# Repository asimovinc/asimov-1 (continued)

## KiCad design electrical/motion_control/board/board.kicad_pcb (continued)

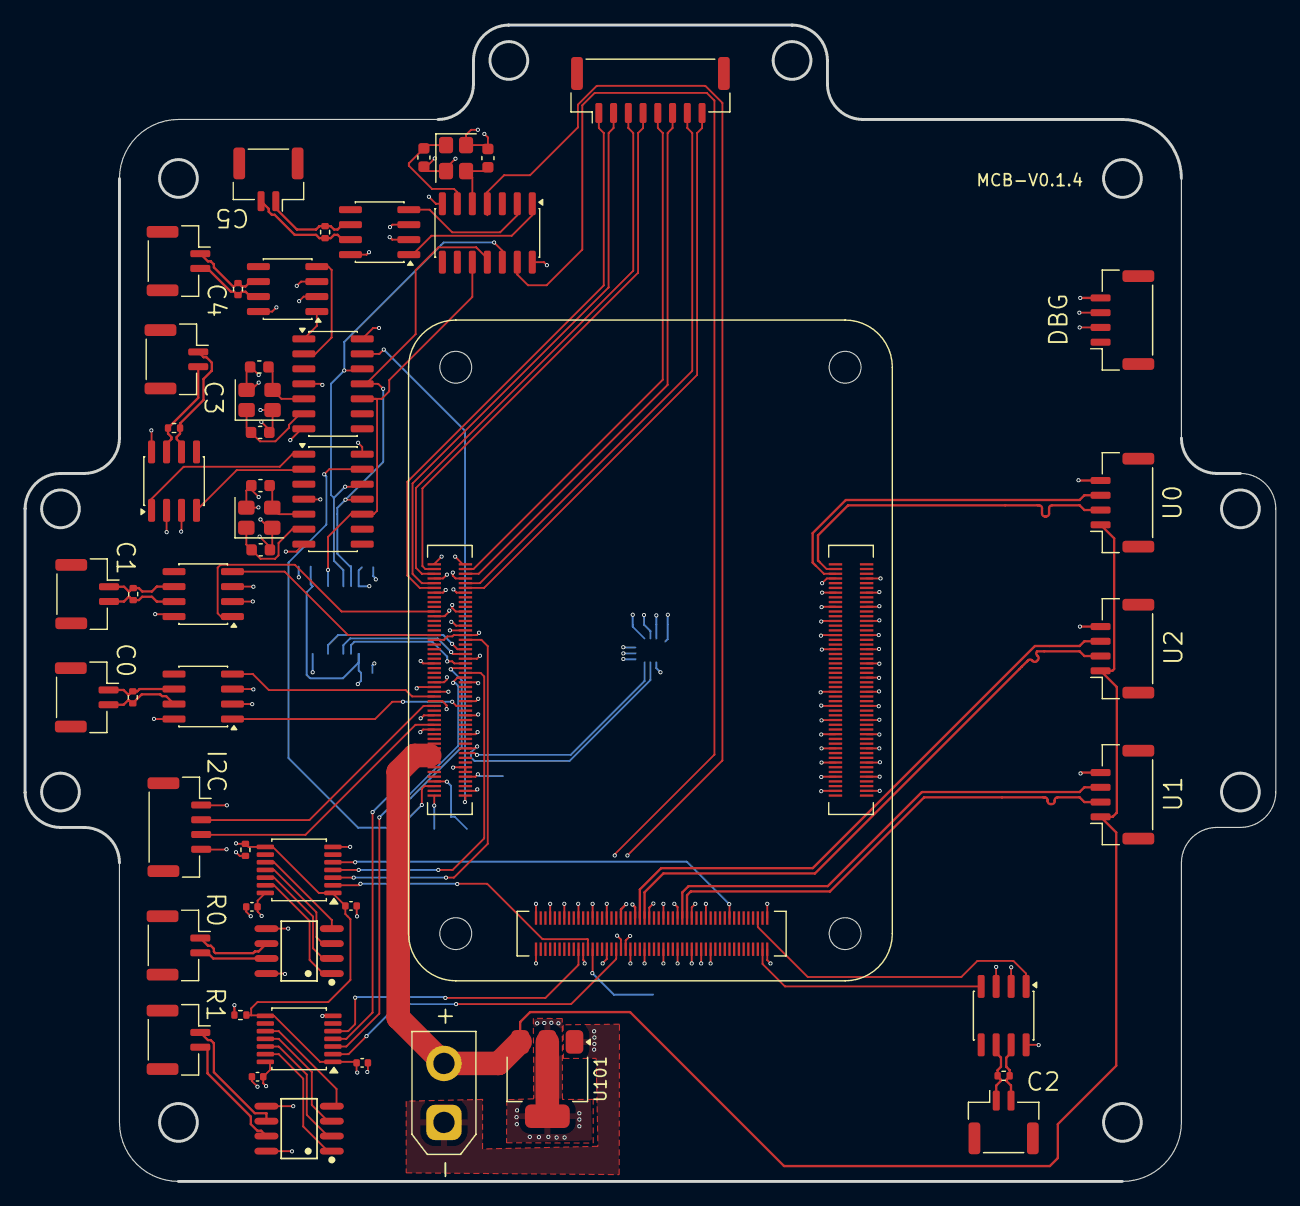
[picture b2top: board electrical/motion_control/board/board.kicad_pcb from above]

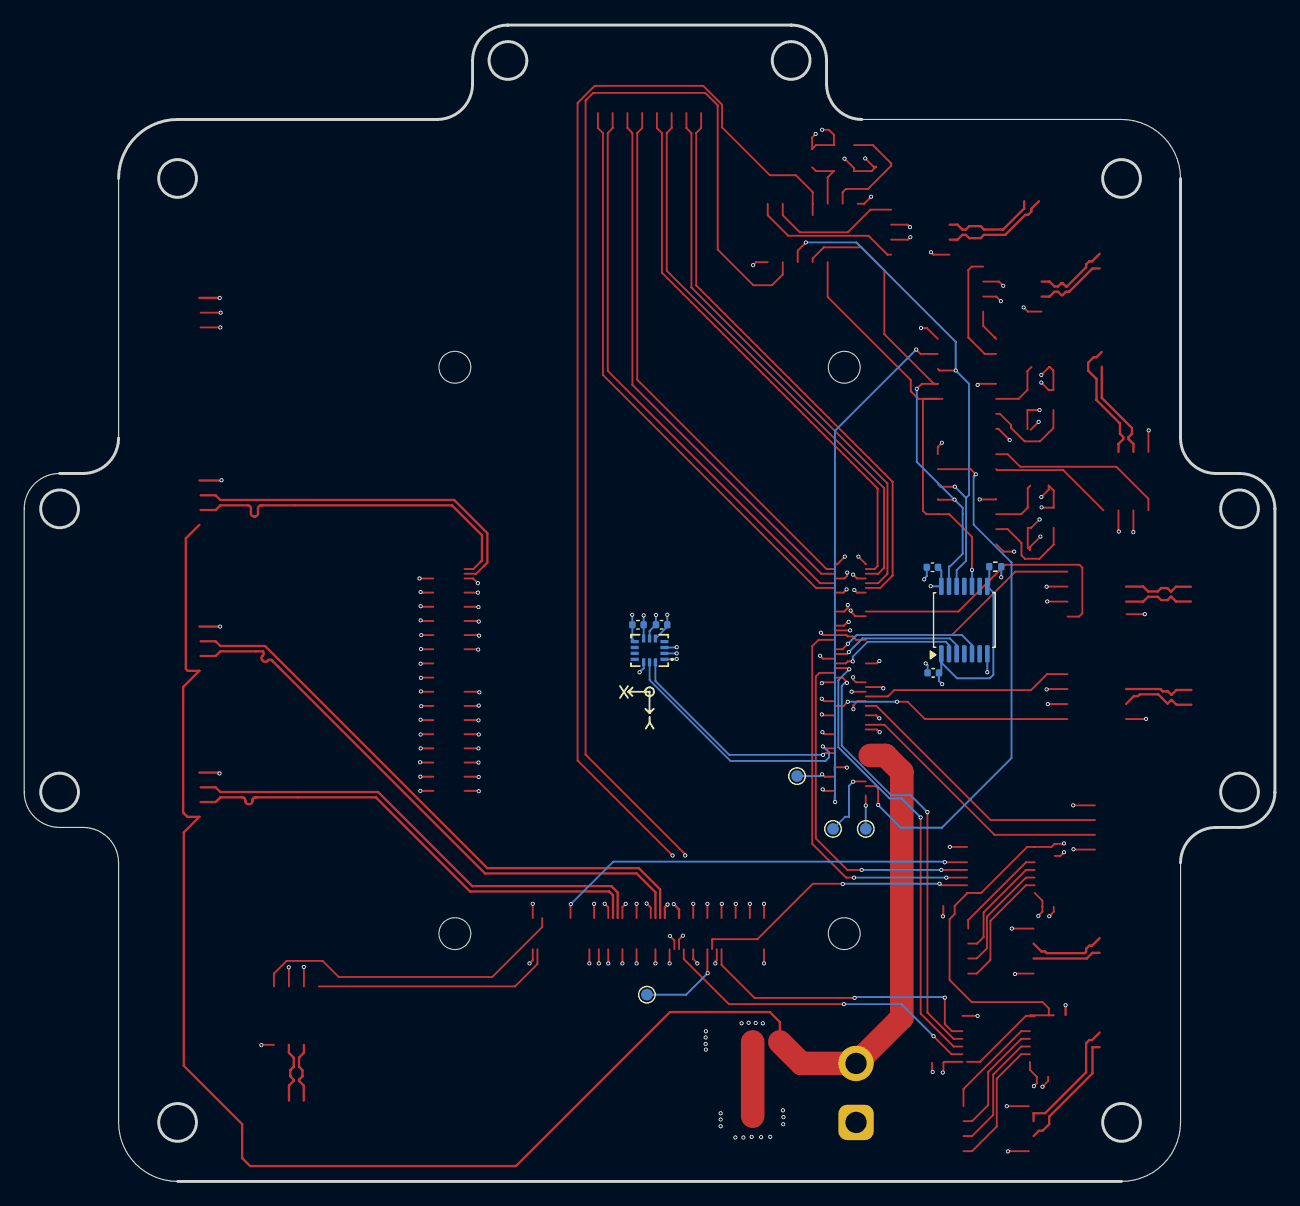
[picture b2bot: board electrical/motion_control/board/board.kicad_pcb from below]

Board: 4 copper layers, 106.0 x 98.0 mm, 64 parts (11 on the bottom side), 90 nets.

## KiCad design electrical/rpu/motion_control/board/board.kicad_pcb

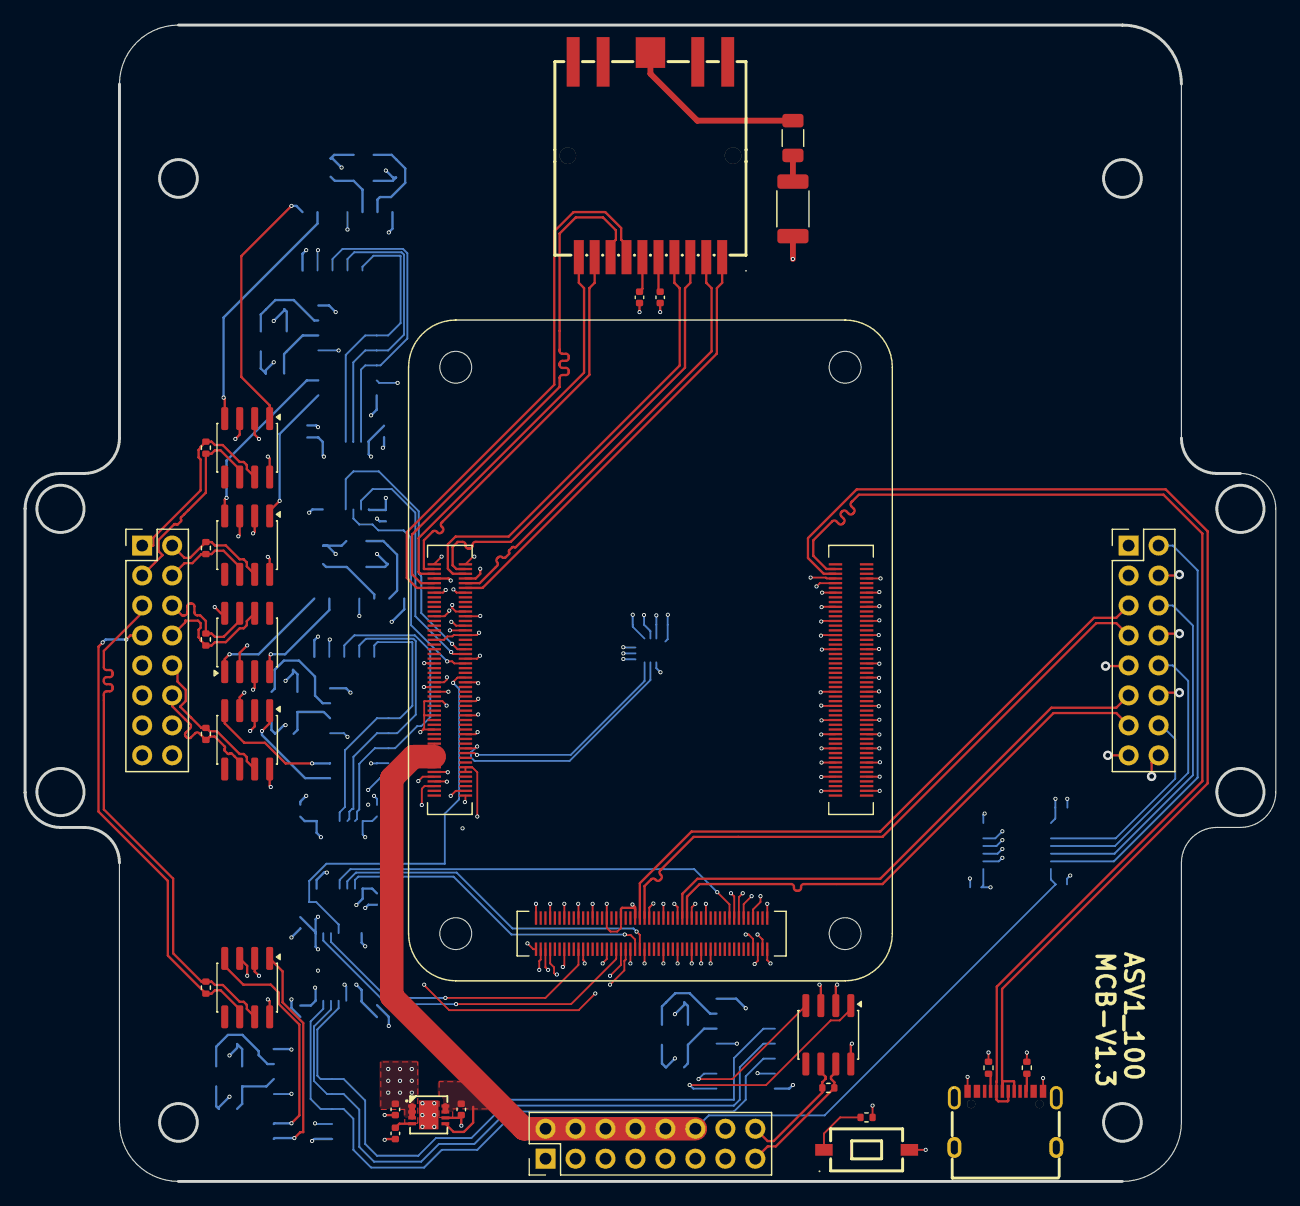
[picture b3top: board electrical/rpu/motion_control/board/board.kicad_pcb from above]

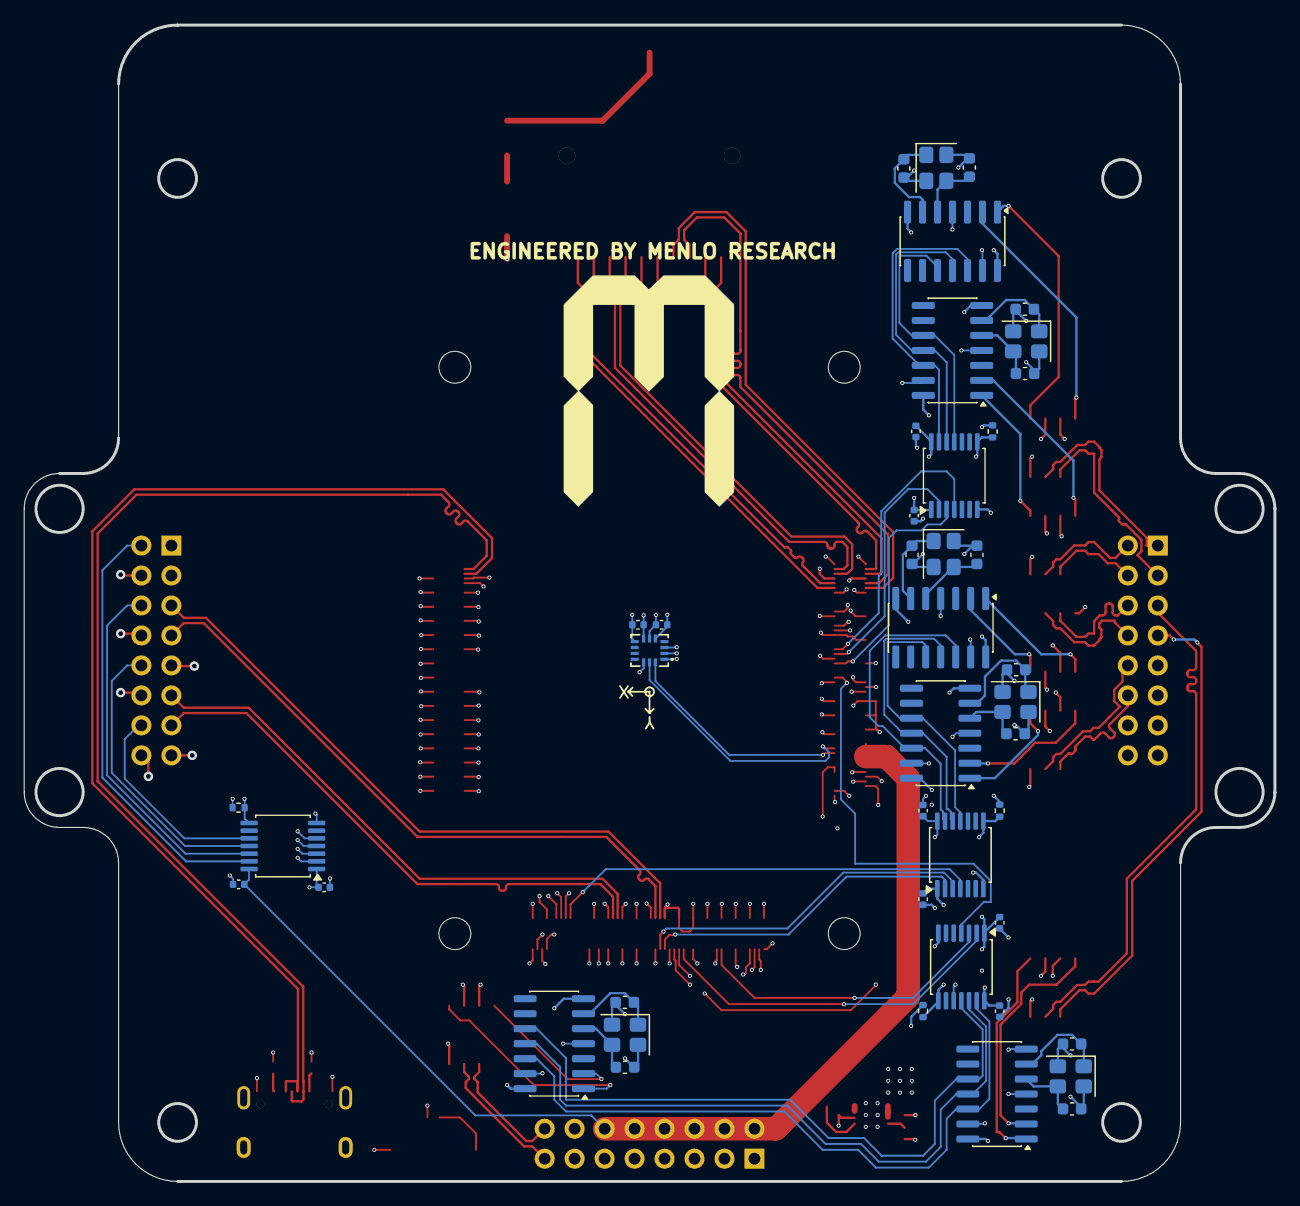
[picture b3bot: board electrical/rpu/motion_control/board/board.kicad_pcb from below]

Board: 4 copper layers, 106.0 x 98.0 mm, 75 parts (43 on the bottom side), 105 nets.

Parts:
C101, C103: 4.7u; C_0402_1005Metric
C102: 1n; C_0402_1005Metric
C201, C202, C204, C205, C501, C502, C503, C504, C505, C506, C507, C508: 100n; C_0402_1005Metric
C203: 1n; C_1206_3216Metric
C601, C602, C603, C604, C605, C606, C607, C608, C609, C610, C611, C612: 20p; C_0603_1608Metric
J101: HEADER_LEFT; PinHeader_2x08_P2.54mm_Vertical
J102: HEADER_BOTTOM; PinHeader_2x08_P2.54mm_Vertical
J103: HEADER_RIGHT; PinHeader_2x08_P2.54mm_Vertical
R201: 1M; R_2010_5025Metric
R202: 100; R_0402_1005Metric
R301, R302: 5.1k; R_0402_1005Metric
R501, R502, R503, R504: 10k; R_0402_1005Metric
R601, R602, R603, R604, R605, R606: 120; R_0402_1005Metric
SW201: TS50810-411-02528; SW-SMD_L6.2-W3.7-LS8.0
U101: ADM7172ACPZ-3.3-R7; DFN-8_L3.0-W3.0-P0.50-BL-EP
U201: Hirose DF40C-100DS-0.4V; radxa_cm5_1
U202: ETH; RJ45-SMD_HR963380AE
U203: LSM6DSVTR; LGA-14_L3.0-W2.5-P0.50-TL
U301: Hirose DF40C-100DS-0.4V; radxa_cm5_2
U401: Hirose DF40C-100DS-0.4V; radxa_cm5_3
U501, U502, U503, U504: TXB0104PW; TSSOP-14_4.4x5mm_P0.65mm
U601, U602, U603, U607, U608, U609: MCP2518FD-xQBB; SOIC-14_3.9x8.7mm_P1.27mm
U604, U605, U606, U610, U611, U612: SN65HVD230; SOIC-8_3.9x4.9mm_P1.27mm
USB301: TYPE-C 16PIN 2MD; USB-C-SMD_TYPE-C-16PIN-2MD-073
Y601, Y602, Y603, Y604, Y605, Y606: 40M; Crystal_SMD_3225-4Pin_3.2x2.5mm

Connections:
+1V8: C503.1, C505.1, C506.1, R502.2, R503.2, R504.2, U201.88 (+1.8v_(Output)), U201.90 (+1.8v_(Output)), U502.1 (VCCA), U502.8 (OE), U503.1 (VCCA), U503.8 (OE), U504.1 (VCCA), U504.8 (OE)
+3V3: C101.1, C201.1, C202.1, C501.1, C504.1, C507.1, C508.1, R501.2, U101.1 (OUT), U101.2 (OUT), U101.3 (SENSE), U203.5 (VDD_IO), U203.8 (VDD), U203.12 (CS), U501.1 (VCCA), U501.8 (OE), U502.14 (VCCB), U503.14 (VCCB), U504.14 (VCCB), U601.14 (VDD), U602.14 (VDD), U603.14 (VDD), U604.3 (VCC), U605.3 (VCC), U606.3 (VCC), U607.14 (VDD), U608.14 (VDD), U609.14 (VDD), U610.3 (VCC), U611.3 (VCC), U612.3 (VCC)
+5V: C103.1, C502.1, J102.2, J102.4, J102.6, J102.8, J102.10, J102.12, U101.5 (EN), U101.7 (VIN), U101.8 (VIN), U201.77 (+5v_(Input)), U201.79 (+5v_(Input)), U201.81 (+5v_(Input)), U201.83 (+5v_(Input)), U201.85 (+5v_(Input)), U201.87 (+5v_(Input)), U501.14 (VCCB)
/J1/GPIO3_B7_3V3: U401.206 (GPIO_3V3_2), U501.3 (A2)
/J1/GPIO3_C0_3V3: U401.204 (GPIO_3V3_1), U501.2 (A1)
/J1/GPIO3_C4_3V3: U401.208 (GPIO_3V3_3), U501.4 (A3)
/J1/GPIO3_D4_3V3: U401.214 (GPIO_3V3_4), U501.5 (A4)
/J1/SPI1_CLK_M2_1V8: U401.283 (GPIO_1V8_12), U503.4 (A3)
/J1/SPI1_CS0: U401.238 (GPIO_3V3_7), U603.13 (~CS)
/J1/SPI1_CS1: U401.294 (GPIO_3V3_9), U608.13 (~CS)
/J1/SPI1_INT0: U401.240 (GPIO_3V3_8), U603.4 (~INT)
/J1/SPI1_INT1: U401.298 (GPIO_3V3_BT_REG_ON), U608.4 (~INT)
/J1/SPI1_MISO_M2_1V8: U401.244 (GPIO_1V8_6), U503.2 (A1)
/J1/SPI1_MOSI_M2_1V8: U401.246 (GPIO_1V8_7), U503.3 (A2)
/J1/SPI4_CS0: U401.287 (GPIO_3V3_13), U601.13 (~CS)
/J1/SPI4_CS1: U401.293 (GPIO_3V3_15), U609.13 (~CS)
/J1/SPI4_INT0: U401.285 (GPIO_3V3_12), U601.4 (~INT)
/J1/SPI4_INT1: U401.289 (GPIO_3V3_14), U609.4 (~INT)
/J1/SPI4_MISO_M0_1V8: U401.236 (GPIO_1V8_HP_DET_L), U504.2 (A1)
/J1/SPI4_MOSI_M0_1V8: U401.220 (GPIO_1V8_3), U504.3 (A2)
/SPI-CAN/SPI0_CLK: U502.11 (B3), U602.10 (SCK), U607.10 (SCK)
/SPI-CAN/SPI0_CS0: U201.95 (nPI_LED_PWR), U602.13 (~CS)
/SPI-CAN/SPI0_CS1: U201.100 (nEXTRST), U607.13 (~CS)
/SPI-CAN/SPI0_INT0: U201.30 (GPIO6), U602.4 (~INT)
/SPI-CAN/SPI0_INT1: U201.28 (GPIO13), U607.4 (~INT)
/SPI-CAN/SPI00_OSC_1: C602.1, U602.6 (OSC1), Y602.1
/SPI-CAN/SPI00_OSC_2: C605.1, U602.5 (OSC2), Y602.3
/SPI-CAN/SPI0_SI: U502.12 (B2), U602.11 (SDI), U607.11 (SDI)
/SPI-CAN/SPI0_SO: U502.13 (B1), U602.12 (SDO), U607.12 (SDO)
/SPI-CAN/SPI1_CLK: U503.11 (B3), U603.10 (SCK), U608.10 (SCK)
/SPI-CAN/SPI01_OSC_1: C607.1, U607.6 (OSC1), Y604.1
/SPI-CAN/SPI01_OSC_2: C610.1, U607.5 (OSC2), Y604.3
/SPI-CAN/SPI1_SI: U503.12 (B2), U603.11 (SDI), U608.11 (SDI)
/SPI-CAN/SPI1_SO: U503.13 (B1), U603.12 (SDO), U608.12 (SDO)
/SPI-CAN/SPI4_CLK: U504.11 (B3), U601.10 (SCK), U609.10 (SCK)
/SPI-CAN/SPI4_SI: U504.12 (B2), U601.11 (SDI), U609.11 (SDI)
/SPI-CAN/SPI4_SO: U504.13 (B1), U601.12 (SDO), U609.12 (SDO)
/SPI-CAN/SPI10_OSC_1: C603.1, U603.6 (OSC1), Y603.1
/SPI-CAN/SPI10_OSC_2: C606.1, U603.5 (OSC2), Y603.3
/SPI-CAN/SPI11_OSC_1: C608.1, U608.6 (OSC1), Y605.1
/SPI-CAN/SPI11_OSC_2: C611.1, U608.5 (OSC2), Y605.3
/SPI-CAN/SPI40_OSC_1: C601.1, U601.6 (OSC1), Y601.1
/SPI-CAN/SPI40_OSC_2: C604.1, U601.5 (OSC2), Y601.3
/SPI-CAN/SPI41_OSC_1: C609.1, U609.6 (OSC1), Y606.1
/SPI-CAN/SPI41_OSC_2: C612.1, U609.5 (OSC2), Y606.3
/TTL-SHIFT/SPI0_CLK_M2_1V8: U201.38 (GPIO11), U502.4 (A3)
/TTL-SHIFT/SPI0_MISO_M2_1V8: U201.40 (GPIO9), U502.2 (A1)
/TTL-SHIFT/SPI0_MOSI_M2_1V8: U201.44 (GPIO10), U502.3 (A2)
/TTL-SHIFT/SPI4_CLK_M0_1V8: U201.50 (GPIO17), U504.4 (A3)
/U13A/CT0: C204.1, U202.5
/U13A/CT1: C205.1, U202.6
/U13A/Ethernet_Pair0_N: U201.10 (Ethernet_Pair0_N), U202.2
/U13A/Ethernet_Pair0_P: U201.12 (Ethernet_Pair0_P), U202.1
/U13A/Ethernet_Pair1_N: U201.6 (Ethernet_Pair1_N), U202.4
/U13A/Ethernet_Pair1_P: U201.4 (Ethernet_Pair1_P), U202.3
/U13A/Ethernet_Pair2_N: U201.9 (Ethernet_Pair2_N), U202.8
/U13A/Ethernet_Pair2_P: U201.11 (Ethernet_Pair2_P), U202.7
/U13A/Ethernet_Pair3_N: U201.5 (Ethernet_Pair3_N), U202.10
/U13A/Ethernet_Pair3_P: U201.3 (Ethernet_Pair3_P), U202.9
/U13A/IMU_I2C7_SCL_M2: U201.80 (SCL0), U203.13 (SCL)
/U13A/IMU_I2C7_SDA_M2: U201.82 (SDA0), U203.14 (SDA)
/U13A/MASKROM_KEY: R202.1, U201.93 (nRPIBOOT)
/U13B/USB2_D+: U301.105 (USB2_P), USB301.A6 (Dp1), USB301.B6 (Dp2)
/U13B/USB2_D-: U301.103 (USB2_N), USB301.A7 (Dn1), USB301.B7 (Dn2)
CAN0+: J101.1, R604.1, U610.7 (CANH)
CAN0-: J101.3, R604.2, U610.6 (CANL)
CAN1+: J101.6, R605.1, U611.7 (CANH)
CAN1-: J101.8, R605.2, U611.6 (CANL)
CAN2+: J102.15, R606.1, U612.7 (CANH)
CAN2-: J102.16, R606.2, U612.6 (CANL)
CAN3+: J101.2, R602.1, U605.7 (CANH)
CAN3-: J101.4, R602.2, U605.6 (CANL)
CAN4+: J101.10, R603.1, U606.7 (CANH)
CAN4-: J101.12, R603.2, U606.6 (CANL)
CAN5+: J101.5, R601.1, U604.7 (CANH)
CAN5-: J101.7, R601.2, U604.6 (CANL)
Earth: C203.2, U202.15
GND: C101.2, C102.2, C103.2, C201.2, C202.2, C204.2, C205.2, C501.2, C502.2, C503.2, C504.2, C505.2, C506.2, C507.2, C508.2, C601.2, C602.2, C603.2, C604.2, C605.2, C606.2, C607.2, C608.2, C609.2, C610.2, C611.2, C612.2, J102.1, J102.3, J102.5, J102.7, J102.9, J102.11, J103.4, J103.8, J103.9, J103.12, J103.15, J103.16, R201.1, R301.1, R302.1, R501.1, R502.1, R503.1, R504.1, SW201.2, U101.6 (GND), U101.9 (EP), U201.1 (GND), U201.2 (GND), U201.7 (GND), U201.8 (GND), U201.13 (GND), U201.14 (GND), U201.22 (GND), U201.23 (GND), U201.32 (GND), U201.33 (GND), U201.42 (GND), U201.43 (GND), U201.52 (GND), U201.53 (GND), U201.59 (GND), U201.60 (GND), U201.65 (GND), U201.66 (GND), U201.71 (GND), U201.74 (GND), U201.98 (GND), U203.1 (SDO/SA0), U203.2 (SDX), U203.3 (SCX), U203.6 (GND), U203.7 (GND), U301.107 (GND), U301.108 (GND), U301.113 (GND), U301.114 (GND), U301.119 (GND), U301.120 (GND), U301.125 (GND), U301.126 (GND), U301.131 (GND), U301.132 (GND), U301.137 (GND), U301.138 (GND), U301.144 (GND), U301.150 (GND), U301.155 (GND), U301.156 (GND), U301.161 (GND), U301.162 (GND), U301.167 (GND), U301.168 (GND), U301.173 (GND), U301.174 (GND), U301.179 (GND), U301.180 (GND), U301.185 (GND), U301.186 (GND), U301.191 (GND), U301.192 (GND), U301.197 (GND), U301.198 (GND), U401.201 (GND), U401.202 (GND), U401.207 (GND), U401.213 (GND), U401.219 (GND), U401.222 (GND), U401.225 (GND), U401.231 (GND), U401.232 (GND), U401.237 (GND), U401.242 (GND), U401.243 (GND), U401.248 (GND), U401.249 (GND), U401.255 (GND), U401.256 (GND), U401.261 (GND), U401.262 (GND), U401.267 (GND), U401.268 (GND), U401.272 (GND), U401.273 (GND), U401.276 (GND), U401.299 (GND), U401.300 (GND), U501.7 (GND), U502.7 (GND), U503.7 (GND), U504.7 (GND), U601.7 (VSS), U602.7 (VSS), U603.7 (VSS), U604.2 (GND), U604.8 (Rs), U605.2 (GND), U605.8 (Rs), U606.2 (GND), U606.8 (Rs), U607.7 (VSS), U608.7 (VSS), U609.7 (VSS), U610.2 (GND), U610.8 (Rs), U611.2 (GND), U611.8 (Rs), U612.2 (GND), U612.8 (Rs), USB301.A1B12 (GND), USB301.B1A12 (GND), Y601.2, Y601.4, Y602.2, Y602.4, Y603.2, Y603.4, Y604.2, Y604.4, Y605.2, Y605.4, Y606.2, Y606.4
GPIO3_B7_5V: J103.6, U501.12 (B2)
GPIO3_C0_5V: J103.2, U501.13 (B1)
GPIO3_C4_5V: J103.10, U501.11 (B3)
GPIO3_D4_5V: J103.14, U501.10 (B4)
unnamed: C203.1, R201.2
unnamed: R202.2, SW201.1
unnamed: C102.1, U101.4 (SS)
unnamed: U601.2 (RXCAN), U604.4 (R)
unnamed: U601.1 (TXCAN), U604.1 (D)
unnamed: U602.2 (RXCAN), U605.4 (R)
unnamed: U602.1 (TXCAN), U605.1 (D)
unnamed: U603.2 (RXCAN), U606.4 (R)
unnamed: U603.1 (TXCAN), U606.1 (D)
unnamed: U607.2 (RXCAN), U610.4 (R)
unnamed: U607.1 (TXCAN), U610.1 (D)
unnamed: U608.2 (RXCAN), U611.4 (R)
unnamed: U608.1 (TXCAN), U611.1 (D)
unnamed: U609.2 (RXCAN), U612.4 (R)
unnamed: U609.1 (TXCAN), U612.1 (D)
unnamed: R301.2, USB301.A5 (CC1)
unnamed: R302.2, USB301.B5 (CC2)
UART2_RX_M0: J103.1, U201.51 (GPIO15)
UART2_TX_M0: J103.3, U201.55 (GPIO14)
USB2_HOST0_D+: J103.7, U401.247 (USB3_HOST1_DM)
USB2_HOST0_D-: J103.5, U401.245 (USB3_HOST1_DP)
USB2_HOST1_D+: J103.13, U401.265 (USB2_HOST2_DM)
USB2_HOST1_D-: J103.11, U401.263 (USB2_HOST2_DP)

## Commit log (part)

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2026-04-17 add sim-model assets and xml
2026-04-20 add asimov-api as submodule, remove empty edge/README.md
2026-04-20 added wiring, added software license
2026-04-20 Prepare electrical information for release, misc changes (#1)
    * added wiring, added software license
    * updated README
2026-04-27 remove submodule for asimov-api
2026-04-27 remove submodule for asimov-api (#3)
2026-04-28 Add fabrication manifest artifact checks
2026-04-29 moved in source files, pending readme
2026-04-30 fleshed out readme
2026-05-12 Updated xml with aligned collision meshes
2026-05-13 feat(software): Add URDF model and conversion tools for IsaacGym training
    Convert Asimov v1 MuJoCo MJCF model to URDF for IsaacGym-based RL training.
    Completes Phase 0.1 of the RL development roadmap.
    ## Changes
    - Add `software/resources/robots/asimov_v1/urdf/asimov_v1.urdf`
    - 28 links (pelvis + legs 14 + arms 10 + waist 1 + neck 2 + toes 2)
    - 27 revolute joints (25 actuated + 2 passive toe joints)
2026-05-14 Simplify fabrication manifest checks
2026-05-14 feat(software): Set up RL training framework with corrected URDF model
    Complete Phase 1 of the RL development plan: port the agibot_x1_train
    IsaacGym training framework to Asimov v1, with a working 12-DOF
    lower-body standing task configuration. Also fix two URDF conversion
    bugs that caused link meshes to render in wrong positions.
    Rewrite the MJCF→URDF converter to parse source XML directly instead
    of going through MuJoCo's compiled model. Fixes two bugs:
2026-05-14 Fix issacgym torch import
2026-05-15 fix(sim2sim): Make MuJoCo deployment script work with Asimov v1
    The sim2sim.py pipeline now runs end-to-end on macOS with the legs-only
    training policy. Fixes a cascade of issues hit while attempting to
    verify the iter-500 checkpoint.
    - Add `autolimits="true"` to the <compiler> element. MuJoCo 3.x rejects
    joints that declare `range` without an explicit `limited` attribute;
    the source MJCF compiled fine via the viewer CLI but failed when
2026-05-16 fix(sim2sim): Match training kinematic structure by stripping non-leg joints
    The sim2sim pipeline was loading the full 27-joint MJCF, causing two
    silent bugs that made policy evaluation impossible. With the legs-only
    MJCF, the policy now controls the correct joints and the upper body
    remains rigidly attached to the pelvis — matching the training-time
    URDF.
    1. Observation indexing was wrong. sim2sim reads
2026-05-16 fix: Stable default pose + reset button + URDF/MJCF verifier
    - config: Rewrite default_joint_angles using balanced-squat formula
    (hip_pitch=∓0.20, knee=±0.40, ankle_pitch=-0.20). COM offset from
    foot midpoint drops from +27 cm to +1.8 cm. Old checkpoints are
    incompatible — must retrain from scratch.
    - make_legs_mjcf.py: Bake non-zero joint `ref` into parent body's
    quat when stripping joints. Fixes left/right elbow rest pose
2026-05-16 final_swing_joint_delta_pos mirror
2026-05-16 increase tracking_lin_vel
2026-05-16 Use old reward scale
2026-05-17 rew_feet_air_time rew_feet_clearance reward
2026-05-17 fix ankle_pitch
2026-05-17 Fix reward
2026-05-17 Update save_interval
2026-05-17 Modify hip pd
2026-05-17 feet_height_walking reward
2026-05-17 Add README
2026-05-17 Modify reward for hip pitch
2026-05-18 Add fabrication manifest artifact checks (#5)
    * Add fabrication manifest artifact checks
    * Simplify fabrication manifest checks
    ---------
2026-05-18 Modify default pose
2026-05-19 Modify final_swing_joint_delta_pos, remove feet_height_walking reward
2026-05-19 Modify PD
2026-05-20 hip_pitch reference uses the FULL sin wave
2026-05-20 Flip right knee and ankle pitch
2026-05-20 Fix parameter
2026-05-23 added 1mm addition for handle, saved at freecad format
2026-06-18 PCB for the head V0
2026-06-18 Fixed C36 placement
